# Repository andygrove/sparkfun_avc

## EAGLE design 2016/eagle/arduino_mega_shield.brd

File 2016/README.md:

# autonomous_vehicle

Arduino source code for an autonomous vehicle using the following components:

1. Arduino Mega 2560
2. Adafruit Ultimate GPS (Serial)
3. Sparkfun HMC6352 magenetometer breakout (I2C)
4. Octasonic HC-SR04 Breakout (SPI)
5. Pololu Qik 2s12v10 motor controller board (Serial)

Need to replace standard SD library with this one that uses soft SPI on pins 10,11,12,13 instead of 50,51,52

https://github.com/adafruit/SD

## GPS

| Arduino | GPS   | Wire color |
|---------|-------|------------|
| 18      | RX    | Gray       |
| 19      | TX    | White      |
| 5V      | VCC   | Blue       |
| GND     | GND   | Purple     |

## Compass

| Arduino | Compass | Wire color |
|---------|---------|------------|
| 20      | SDA     | Gray       |
| 21      | SCL     | White      |
| 5V      | VCC     | Blue       |
| GND     | GND     | Purple     |

## Qik

| Arduino | Component   | Wire color |
|---------|-------------|------------|
| 62 (A8) | Qik RESET   | White      |
| 63 (A9) | Qik TX      | Gray       |
| 64 (A10)| Qik RX      | Purple     |
| GND     | Qik GND     | Black      |

## Octasonic

| Arduino | Octasonic | Wire color |
|---------|-----------|------------|
| 50      | MISO      | Yellow     |
| 51      | MOSI      | Green      |
| 52      | SCK       | Orange     |
| 53      | SS        | Blue       |

## SD Shield

| Arduino | Component   | Wire color |
|---------|-------------|------------|
| 10-13   | SD shield   | N/A        |

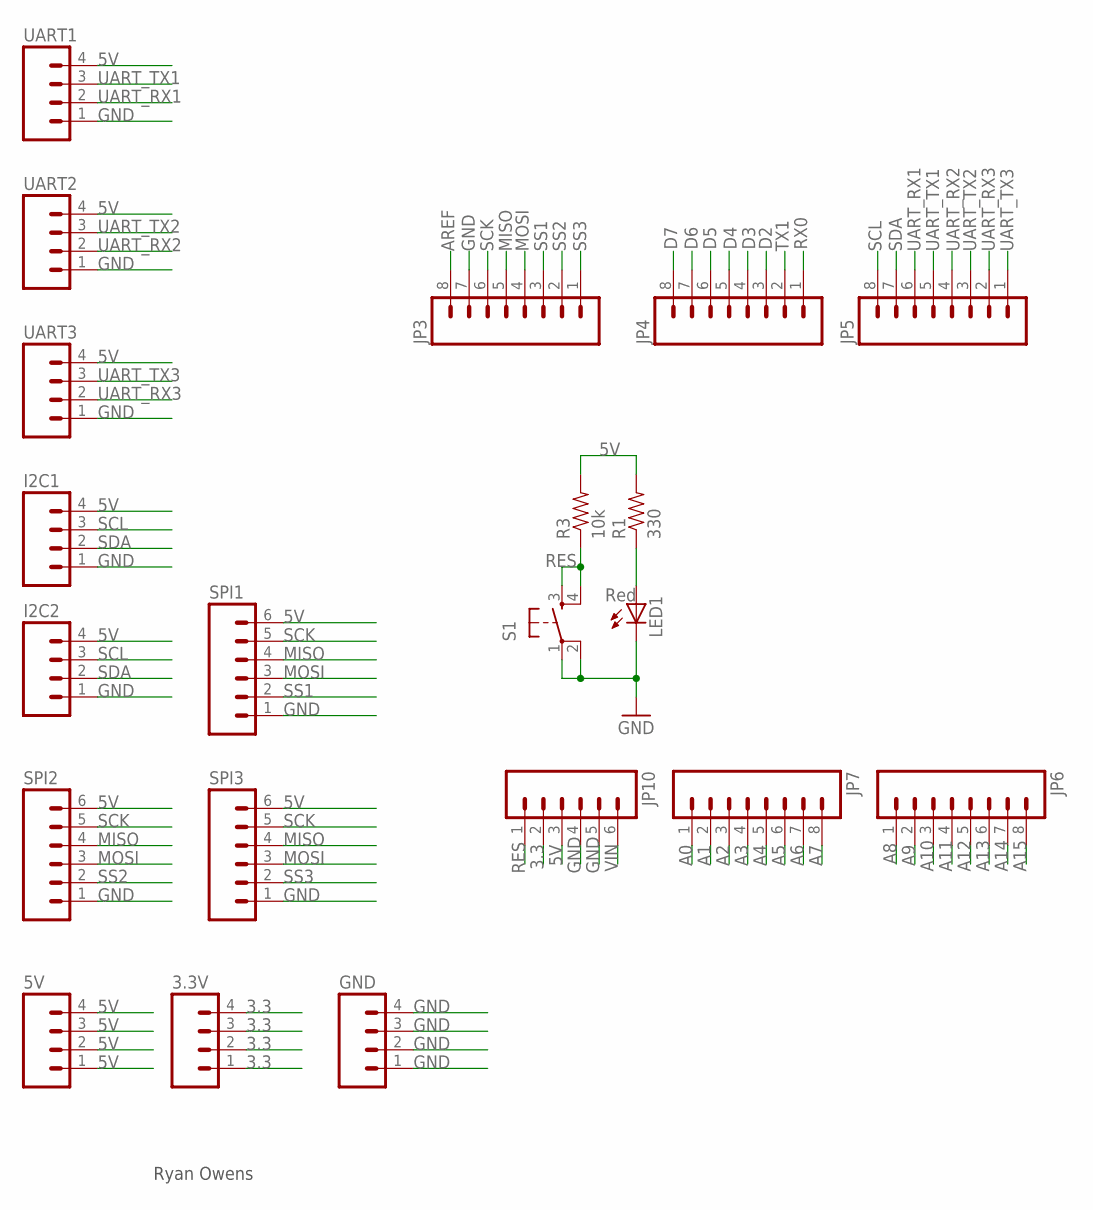
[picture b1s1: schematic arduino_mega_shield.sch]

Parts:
3.3V, 5V: M04LOCK; 1X04_LOCK
GND: M04LOCK; 1X04_LOCK
I2C1, I2C2: M04LOCK; 1X04_LOCK
JP3, JP4, JP5, JP6, JP7: M08LOCK; 1X08_LOCK
JP10: M06LOCK; 1X06_LOCK
LED1: Red; LED5MM
R1: 330; AXIAL-0.3
R3: 10k; AXIAL-0.3
S1: TAC_SWITCHPTH; TACTILE-PTH
SPI1, SPI2, SPI3: M06LOCK; 1X06_LOCK
UART1, UART2, UART3: M04LOCK; 1X04_LOCK

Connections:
3.3: 3.3V.1, 3.3V.2, 3.3V.3, 3.3V.4, JP10.2
5V: 5V.1, 5V.2, 5V.3, 5V.4, I2C1.4, I2C2.4, JP10.3, R1.P$2 (2), R3.P$2 (2), SPI1.6, SPI2.6, SPI3.6, UART1.4, UART2.4, UART3.4
A0: JP7.1
A1: JP7.2
A2: JP7.3
A3: JP7.4
A4: JP7.5
A5: JP7.6
A6: JP7.7
A7: JP7.8
A8: JP6.1
A9: JP6.2
A10: JP6.3
A11: JP6.4
A12: JP6.5
A13: JP6.6
A14: JP6.7
A15: JP6.8
AREF: JP3.8
D2: JP4.3
D3: JP4.4
D4: JP4.5
D5: JP4.6
D6: JP4.7
D7: JP4.8
GND: GND.1, GND.2, GND.3, GND.4, I2C1.1, I2C2.1, JP3.7, JP10.4, JP10.5, LED1.K (C), S1.1, S1.2, SPI1.1, SPI2.1, SPI3.1, UART1.1, UART2.1, UART3.1
MISO: JP3.5, SPI1.4, SPI2.4, SPI3.4
MOSI: JP3.4, SPI1.3, SPI2.3, SPI3.3
unnamed: LED1.A, R1.P$1 (1)
RES: JP10.1, R3.P$1 (1), S1.3, S1.4
RX0: JP4.1
SCK: JP3.6, SPI1.5, SPI2.5, SPI3.5
SCL: I2C1.3, I2C2.3, JP5.8
SDA: I2C1.2, I2C2.2, JP5.7
SS1: JP3.3, SPI1.2
SS2: JP3.2, SPI2.2
SS3: JP3.1, SPI3.2
TX1: JP4.2
UART_RX1: JP5.6, UART1.2
UART_RX2: JP5.4, UART2.2
UART_RX3: JP5.2, UART3.2
UART_TX1: JP5.5, UART1.3
UART_TX2: JP5.3, UART2.3
UART_TX3: JP5.1, UART3.3
VIN: JP10.6

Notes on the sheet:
Ryan Owens

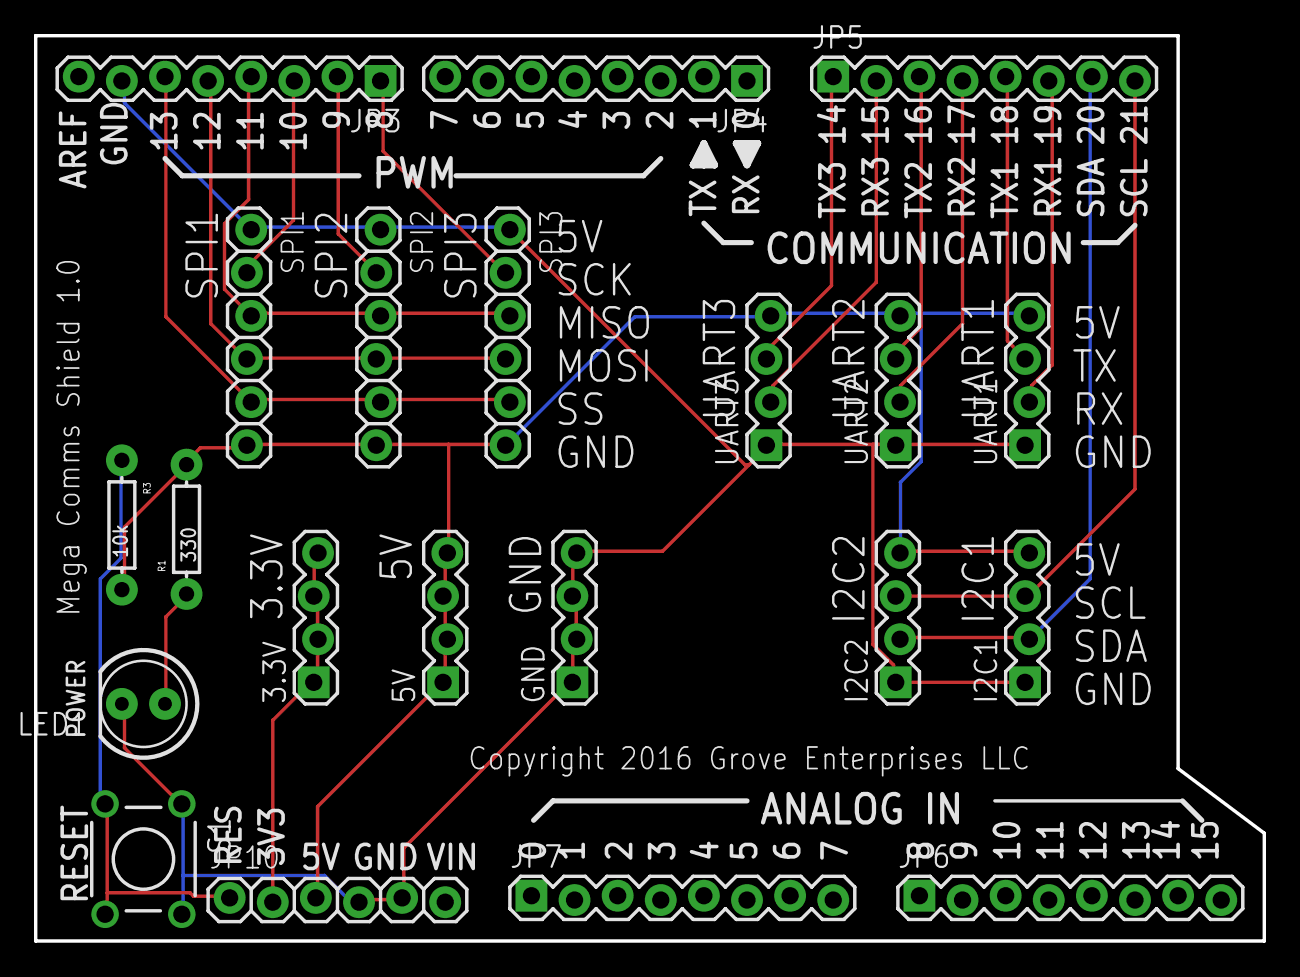
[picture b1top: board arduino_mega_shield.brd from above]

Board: 2 copper layers, 72.4 x 53.3 mm, 21 parts (0 on the bottom side), 19 nets.

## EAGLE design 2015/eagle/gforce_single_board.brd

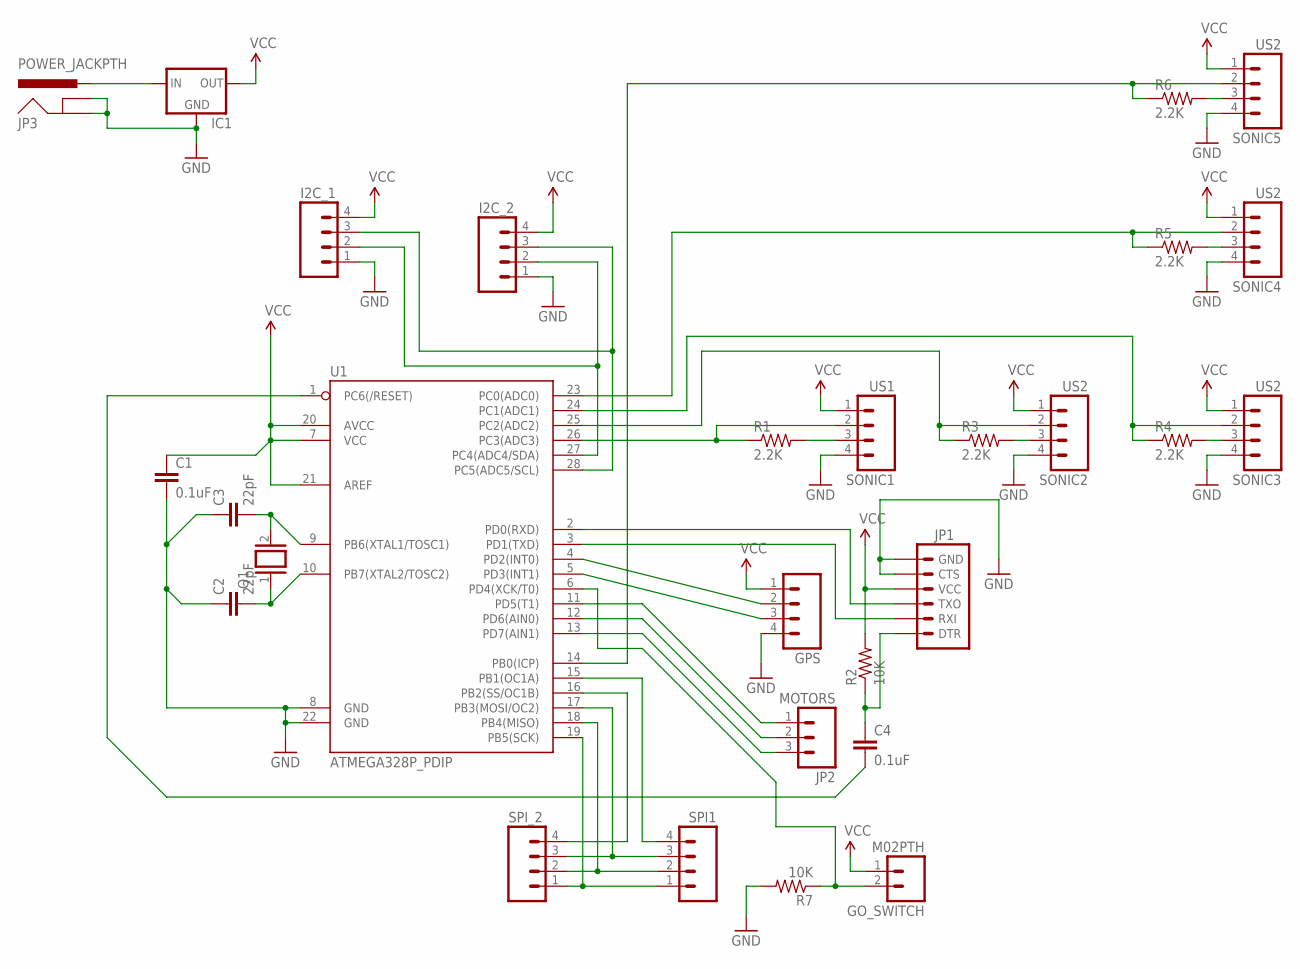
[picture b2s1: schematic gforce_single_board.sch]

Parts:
C1, C4: 0.1uF; CAP-PTH-SMALL
C2, C3: 22pF; CAP-PTH-SMALL
GO_SWITCH: M02PTH; 1X02
GPS: M04PTH; 1X04
I2C_1, I2C_2: M04PTH; 1X04
IC1: V_REG_78XX-TO-220; TO-220-ALT
JP1: ARDUINO_SERIAL_PROGRAMPTH; 1X06
JP2: MOTORS; 1X03
JP3: POWER_JACKPTH; POWER_JACK_PTH
Q1: XTAL/S; QS
R1, R3, R4, R5, R6: 2.2K; AXIAL-0.4
R2, R7: 10K; AXIAL-0.4
SONIC1: US1; 1X04
SONIC2, SONIC3, SONIC4, SONIC5: US2; 1X04
SPI1: M04PTH; 1X04
SPI_2: M04PTH; 1X04
U1: ATMEGA328P_PDIP; DIL28-3

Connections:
GND: C1.2, C2.1, C3.1, GPS.4, I2C_1.1, I2C_2.1, IC1.GND, JP1.5 (CTS), JP1.6 (GND), JP3.GND, JP3.GNDBREAK, R7.P$2 (2), SONIC1.4, SONIC2.4, SONIC3.4, SONIC4.4, SONIC5.4, U1.8 (GND), U1.22 (GND)
MISO: SPI1.2, SPI_2.2, U1.18 (PB4(MISO))
MOSI: SPI1.3, SPI_2.3, U1.17 (PB3(MOSI/OC2))
unnamed: I2C_1.2, I2C_2.2, U1.27 (PC4(ADC4/SDA))
unnamed: I2C_1.3, I2C_2.3, U1.28 (PC5(ADC5/SCL))
unnamed: GPS.2, U1.4 (PD2(INT0))
unnamed: GPS.3, U1.5 (PD3(INT1))
unnamed: C3.2, Q1.2, U1.9 (PB6(XTAL1/TOSC1))
unnamed: C2.2, Q1.1, U1.10 (PB7(XTAL2/TOSC2))
unnamed: JP1.2 (RXI), U1.3 (PD1(TXD))
unnamed: JP1.3 (TXO), U1.2 (PD0(RXD))
unnamed: C4.2, U1.1 (PC6(/RESET))
unnamed: C4.1, JP1.1 (DTR), R2.P$1 (1)
unnamed: R3.P$2 (2), SONIC2.3
unnamed: R3.P$1 (1), SONIC2.2, U1.25 (PC2(ADC2))
unnamed: JP2.1, U1.11 (PD5(T1))
unnamed: R4.P$2 (2), SONIC3.3
unnamed: R4.P$1 (1), SONIC3.2, U1.24 (PC1(ADC1))
unnamed: R6.P$2 (2), SONIC5.3
unnamed: R6.P$1 (1), SONIC5.2, U1.14 (PB0(ICP))
unnamed: JP2.2, U1.12 (PD6(AIN0))
unnamed: R5.P$2 (2), SONIC4.3
unnamed: R5.P$1 (1), SONIC4.2, U1.23 (PC0(ADC0))
unnamed: JP2.3, U1.13 (PD7(AIN1))
unnamed: SPI_2.4, U1.16 (PB2(SS/OC1B))
unnamed: SPI1.4, U1.15 (PB1(OC1A))
unnamed: GO_SWITCH.2, R7.P$1 (1), U1.6 (PD4(XCK/T0))
unnamed: IC1.IN, JP3.PWR
SCK: SPI1.1, SPI_2.1, U1.19 (PB5(SCK))
SONIC1_ECHO: R1.P$2 (2), SONIC1.3
SONIC1_TRIGGER: R1.P$1 (1), SONIC1.2, U1.26 (PC3(ADC3))
VCC: C1.1, GO_SWITCH.1, GPS.1, I2C_1.4, I2C_2.4, IC1.OUT, JP1.4 (VCC), R2.P$2 (2), SONIC1.1, SONIC2.1, SONIC3.1, SONIC4.1, SONIC5.1, U1.7 (VCC), U1.20 (AVCC), U1.21 (AREF)

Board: 2 copper layers, 28 parts (0 on the bottom side), 32 nets, no tracks yet.

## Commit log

2014-11-28 import files
2014-11-28 designs for g-force 2
2014-11-28 save
2014-12-14 change angle wall tab to slot
2014-12-14 change side wall slot to tab
2014-12-14 remove old sensor holes
2014-12-14 new sensor mounting holes
2014-12-14 P1 order
2015-03-08 saving progress
2015-03-15 new version
2015-04-01 new schematic
2015-04-01 version ordered (plus missing pin labels for motor controller)
2016-02-07 add new files
2016-02-21 working on mega shield
2016-02-21 move labels to correct layer
2016-03-06 new wiring
2016-03-06 abondon custom board idea
2016-03-06 code cleanup
2016-03-06 test run 3/6/16
2016-03-06 add log
2016-03-06 logs
2016-03-08 add indicator LEDs

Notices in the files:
2016/eagle/arduino_mega_shield.brd:
Copyright 2016 Grove Enterprises LLC
parts and their libraries:
SparkFun-Passives: Licensing: Creative Commons ShareAlike 4.0 International - https://creativecommons.org/licenses/by-sa/4.0
